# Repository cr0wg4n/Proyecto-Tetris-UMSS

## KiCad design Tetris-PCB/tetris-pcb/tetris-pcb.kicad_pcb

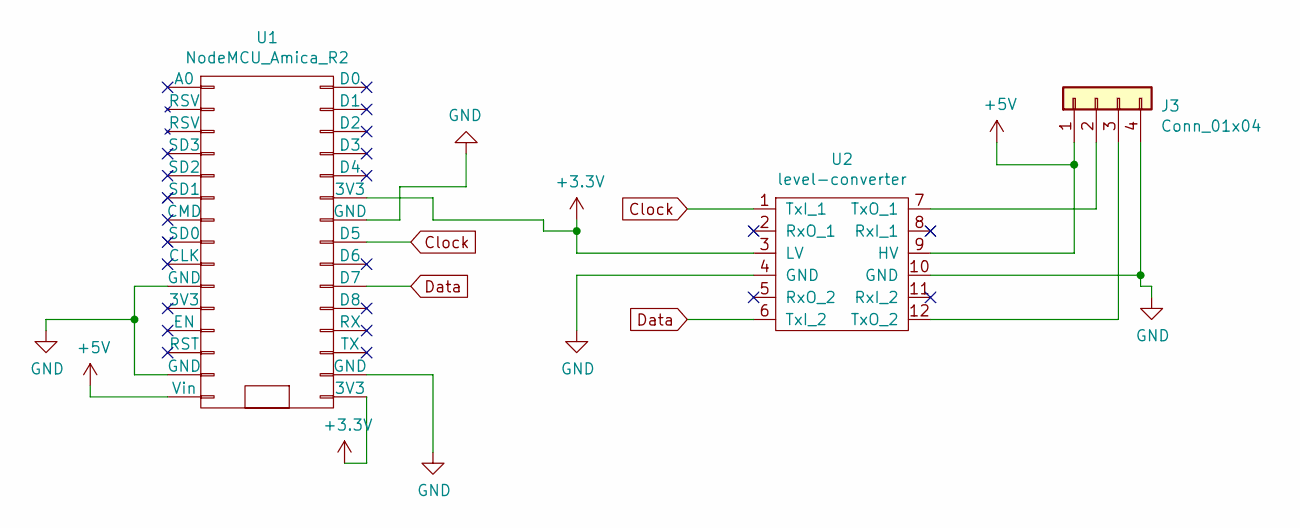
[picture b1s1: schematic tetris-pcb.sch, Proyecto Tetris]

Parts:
J3: Conn_01x04; Molex_KK-254_AE-6410-04A_1x04_P2.54mm_Vertical
U1: NodeMCU_Amica_R2
U2: level-converter; level_converter

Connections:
+3V3: U1.16 (3V3), U1.25 (3V3), U2.3 (LV)
+5V: J3.1, U1.15 (Vin), U2.9 (HV)
Clock: U1.23 (D5), U2.1 (TxI_1)
Data: U1.21 (D7), U2.6 (TxI_2)
GND: J3.4, U1.10 (GND), U1.14 (GND), U1.17 (GND), U1.24 (GND), U2.4 (GND), U2.10 (GND)
unnamed: J3.2, U2.7 (TxO_1)
unnamed: J3.3, U2.12 (TxO_2)

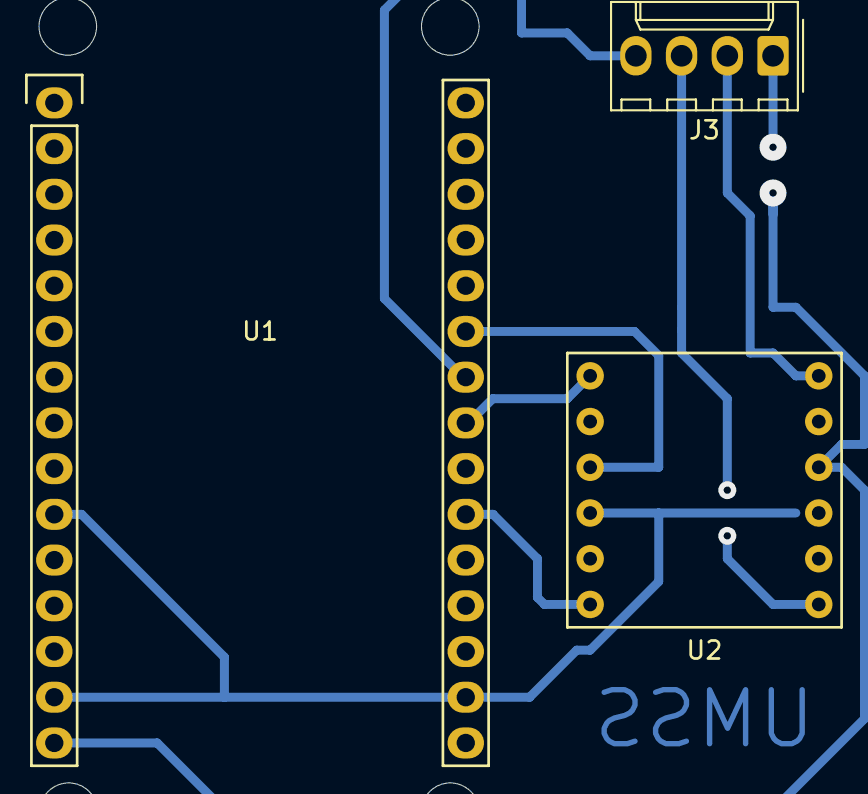
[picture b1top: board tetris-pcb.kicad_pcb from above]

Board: 2 copper layers, 3 parts (0 on the bottom side), 7 nets.

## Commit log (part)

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2019-05-28 server agregado
2019-05-30 agregando codigo para el hardware
2019-06-01 add library
2019-06-01 Tetris Backend
2019-06-02 cambios sabado en grupo
2019-06-02 remove vscode data
2019-06-03 agregando algoritmo de conversion de matriz
2019-06-08 Refactoring Tetris
2019-06-08 agregando python .gitignore y requeriments.txt
2019-06-08 verificando repo
2019-06-20 agregando stm32duino
2019-06-20 moviendo tetris hardware
2019-06-20 SPI interface added to STM
2019-06-22 Add ESP8266 WIFI client
2019-06-23 modicando el servidor para deply
2019-06-23 add gitignore to esp8266
2019-06-23 eliminando archivos inecesarios
2019-06-23 agregando ejemplo de control led
2019-06-23 interfaz de usuario
2019-06-26 add CORS permisions
2019-06-26 servicios agregados
2019-06-27 aumento de keys
2019-06-27 draw matrix
2019-06-28 algoritmo de serializacion pasado a python
2019-06-28 buscando mejoras de performance
2019-06-28 ya envia y dibuja
2019-06-28 WIFI dedicado
2019-06-28 [ADD] Backend Tetris
2019-06-30 agregando tetris
2019-06-30 array format
2019-07-14 Agregado bootstrap y algo de estilo
2019-07-14 Mas estilos
2019-07-14 Aun mas estilo
2019-07-23 cambios con el team
2019-07-26 UI-control-2
2019-07-26 Interfaz para el dibujar la pantalla
2019-07-27 Funcionalidad de selección de color para cada led
2019-07-28 Servicio de envio de matriz de leds
2019-07-31 ordenamiento de carpetas
2019-07-31 3d desings added
2019-08-01 agregando visualizador de musica
2019-11-12 increment colors
2021-03-11 Bump elliptic from 6.5.0 to 6.5.4 in /UI-control-Ionic
    Bumps [elliptic](https://github.com/indutny/elliptic) from 6.5.0 to 6.5.4.
    - [Release notes](https://github.com/indutny/elliptic/releases)
    - [Commits](https://github.com/indutny/elliptic/compare/v6.5.0...v6.5.4)
2021-05-09 Bump handlebars from 4.1.2 to 4.7.7 in /UI-control-Ionic
    Bumps [handlebars](https://github.com/wycats/handlebars.js) from 4.1.2 to 4.7.7.
    - [Release notes](https://github.com/wycats/handlebars.js/releases)
    - [Changelog](https://github.com/handlebars-lang/handlebars.js/blob/master/release-notes.md)
    - [Commits](https://github.com/wycats/handlebars.js/compare/v4.1.2...v4.7.7)
2021-05-10 Bump url-parse from 1.4.7 to 1.5.1 in /UI-control-Ionic
    Bumps [url-parse](https://github.com/unshiftio/url-parse) from 1.4.7 to 1.5.1.
    - [Release notes](https://github.com/unshiftio/url-parse/releases)
    - [Commits](https://github.com/unshiftio/url-parse/compare/1.4.7...1.5.1)
2021-05-11 Bump lodash from 4.17.15 to 4.17.21 in /UI-control-Ionic
    Bumps [lodash](https://github.com/lodash/lodash) from 4.17.15 to 4.17.21.
    - [Release notes](https://github.com/lodash/lodash/releases)
    - [Commits](https://github.com/lodash/lodash/compare/4.17.15...4.17.21)
2021-05-11 Bump hosted-git-info from 2.7.1 to 2.8.9 in /UI-control-Ionic
    Bumps [hosted-git-info](https://github.com/npm/hosted-git-info) from 2.7.1 to 2.8.9.
    - [Release notes](https://github.com/npm/hosted-git-info/releases)
    - [Changelog](https://github.com/npm/hosted-git-info/blob/v2.8.9/CHANGELOG.md)
    - [Commits](https://github.com/npm/hosted-git-info/compare/v2.7.1...v2.8.9)
2021-05-26 Bump browserslist from 4.6.6 to 4.16.6 in /UI-control-Ionic
    Bumps [browserslist](https://github.com/browserslist/browserslist) from 4.6.6 to 4.16.6.
    - [Release notes](https://github.com/browserslist/browserslist/releases)
    - [Changelog](https://github.com/browserslist/browserslist/blob/main/CHANGELOG.md)
    - [Commits](https://github.com/browserslist/browserslist/compare/4.6.6...4.16.6)
2021-05-29 Bump dns-packet from 1.3.1 to 1.3.4 in /UI-control-Ionic
    Bumps [dns-packet](https://github.com/mafintosh/dns-packet) from 1.3.1 to 1.3.4.
    - [Release notes](https://github.com/mafintosh/dns-packet/releases)
    - [Changelog](https://github.com/mafintosh/dns-packet/blob/master/CHANGELOG.md)
    - [Commits](https://github.com/mafintosh/dns-packet/compare/v1.3.1...v1.3.4)
2021-10-06 Bump url-parse from 1.4.7 to 1.5.3 in /UI-control-Ionic
    Bumps [url-parse](https://github.com/unshiftio/url-parse) from 1.4.7 to 1.5.3.
    - [Release notes](https://github.com/unshiftio/url-parse/releases)
    - [Commits](https://github.com/unshiftio/url-parse/compare/1.4.7...1.5.3)
    ---
    updated-dependencies:
    - dependency-name: url-parse
2022-01-14 Bump follow-redirects from 1.7.0 to 1.14.7 in /UI-control-Ionic
    Bumps [follow-redirects](https://github.com/follow-redirects/follow-redirects) from 1.7.0 to 1.14.7.
    - [Release notes](https://github.com/follow-redirects/follow-redirects/releases)
    - [Commits](https://github.com/follow-redirects/follow-redirects/compare/v1.7.0...v1.14.7)
    ---
    updated-dependencies:
    - dependency-name: follow-redirects
2022-01-15 Bump shelljs from 0.8.3 to 0.8.5 in /UI-control-Ionic
    Bumps [shelljs](https://github.com/shelljs/shelljs) from 0.8.3 to 0.8.5.
    - [Release notes](https://github.com/shelljs/shelljs/releases)
    - [Changelog](https://github.com/shelljs/shelljs/blob/master/CHANGELOG.md)
    - [Commits](https://github.com/shelljs/shelljs/compare/v0.8.3...v0.8.5)
    ---
    updated-dependencies:
2022-02-11 Bump karma from 4.1.0 to 6.3.14 in /UI-control-Ionic
    Bumps [karma](https://github.com/karma-runner/karma) from 4.1.0 to 6.3.14.
    - [Release notes](https://github.com/karma-runner/karma/releases)
    - [Changelog](https://github.com/karma-runner/karma/blob/master/CHANGELOG.md)
    - [Commits](https://github.com/karma-runner/karma/compare/v4.1.0...v6.3.14)
    ---
    updated-dependencies:
2022-02-13 Bump follow-redirects from 1.7.0 to 1.14.8 in /UI-control-Ionic
    Bumps [follow-redirects](https://github.com/follow-redirects/follow-redirects) from 1.7.0 to 1.14.8.
    - [Release notes](https://github.com/follow-redirects/follow-redirects/releases)
    - [Commits](https://github.com/follow-redirects/follow-redirects/compare/v1.7.0...v1.14.8)
    ---
    updated-dependencies:
    - dependency-name: follow-redirects
2022-02-27 Bump url-parse from 1.4.7 to 1.5.10 in /UI-control-Ionic
    Bumps [url-parse](https://github.com/unshiftio/url-parse) from 1.4.7 to 1.5.10.
    - [Release notes](https://github.com/unshiftio/url-parse/releases)
    - [Commits](https://github.com/unshiftio/url-parse/compare/1.4.7...1.5.10)
    ---
    updated-dependencies:
    - dependency-name: url-parse
2022-03-02 Bump karma from 4.1.0 to 6.3.16 in /UI-control-Ionic
    Bumps [karma](https://github.com/karma-runner/karma) from 4.1.0 to 6.3.16.
    - [Release notes](https://github.com/karma-runner/karma/releases)
    - [Changelog](https://github.com/karma-runner/karma/blob/master/CHANGELOG.md)
    - [Commits](https://github.com/karma-runner/karma/compare/v4.1.0...v6.3.16)
    ---
    updated-dependencies:
2022-06-01 Bump eventsource from 1.0.7 to 1.1.1 in /UI-control-Ionic
    Bumps [eventsource](https://github.com/EventSource/eventsource) from 1.0.7 to 1.1.1.
    - [Release notes](https://github.com/EventSource/eventsource/releases)
    - [Changelog](https://github.com/EventSource/eventsource/blob/master/HISTORY.md)
    - [Commits](https://github.com/EventSource/eventsource/compare/v1.0.7...v1.1.1)
    ---
    updated-dependencies:
2022-06-03 Bump @angular/core from 7.2.15 to 11.0.5 in /UI-control-Ionic
    Bumps [@angular/core](https://github.com/angular/angular/tree/HEAD/packages/core) from 7.2.15 to 11.0.5.
    - [Release notes](https://github.com/angular/angular/releases)
    - [Changelog](https://github.com/angular/angular/blob/main/CHANGELOG.md)
    - [Commits](https://github.com/angular/angular/commits/11.0.5/packages/core)
    ---
    updated-dependencies:
2022-09-08 Bump jszip from 3.2.2 to 3.10.1 in /UI-control-Ionic
    Bumps [jszip](https://github.com/Stuk/jszip) from 3.2.2 to 3.10.1.
    - [Release notes](https://github.com/Stuk/jszip/releases)
    - [Changelog](https://github.com/Stuk/jszip/blob/main/CHANGES.md)
    - [Commits](https://github.com/Stuk/jszip/compare/v3.2.2...v3.10.1)
    ---
    updated-dependencies:
2022-10-30 Bump socket.io-parser and karma in /UI-control-Ionic
    Bumps [socket.io-parser](https://github.com/socketio/socket.io-parser) to 4.2.1 and updates ancestor dependency [karma](https://github.com/karma-runner/karma). These dependencies need to be updated t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
    Updates `socket.io-parser` from 3.2.0 to 4.2.1
    - [Release notes](https://github.com/socketio/socket.io-parser/releases)
    - [Changelog](https://github.com/socketio/socket.io-parser/blob/main/CHANGELOG.md)
    - [Commits](https://github.com/socketio/socket.io-parser/compare/3.2.0...4.2.1)
    Updates `karma` from 4.1.0 to 6.4.1
2022-11-23 Bump engine.io and karma in /UI-control-Ionic
    Bumps [engine.io](https://github.com/socketio/engine.io) to 6.2.1 and updates ancestor dependency [karma](https://github.com/karma-runner/karma). These dependencies need to be updated together.
    Updates `engine.io` from 3.2.1 to 6.2.1
    - [Release notes](https://github.com/socketio/engine.io/releases)
    - [Changelog](https://github.com/socketio/engine.io/blob/main/CHANGELOG.md)
    - [Commits](https://github.com/socketio/engine.io/compare/3.2.1...6.2.1)
    Updates `karma` from 4.1.0 to 6.4.1
2022-12-06 Bump qs, body-parser and express in /Tetris-Server
    Bumps [qs](https://github.com/ljharb/qs) to 6.11.0 and updates ancestor dependencies [qs](https://github.com/ljharb/qs), [body-parser](https://github.com/expressjs/body-parser) and [express](https://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
    Updates `qs` from 6.7.0 to 6.11.0
    - [Release notes](https://github.com/ljharb/qs/releases)
    - [Changelog](https://github.com/ljharb/qs/blob/main/CHANGELOG.md)
    - [Commits](https://github.com/ljharb/qs/compare/v6.7.0...v6.11.0)
    Updates `body-parser` from 1.19.0 to 1.20.1
2022-12-06 Bump decode-uri-component from 0.2.0 to 0.2.2 in /UI-control-Ionic
    Bumps [decode-uri-component](https://github.com/SamVerschueren/decode-uri-component) from 0.2.0 to 0.2.2.
    - [Release notes](https://github.com/SamVerschueren/decode-uri-component/releases)
    - [Commits](https://github.com/SamVerschueren/decode-uri-component/compare/v0.2.0...v0.2.2)
    ---
    updated-dependencies:
    - dependency-name: decode-uri-component
2022-12-10 Bump express from 4.17.0 to 4.17.3 in /Tetris-Server
    Bumps [express](https://github.com/expressjs/express) from 4.17.0 to 4.17.3.
    - [Release notes](https://github.com/expressjs/express/releases)
    - [Changelog](https://github.com/expressjs/express/blob/master/History.md)
    - [Commits](https://github.com/expressjs/express/compare/4.17.0...4.17.3)
    ---
    updated-dependencies:
2022-12-11 Bump qs from 6.5.2 to 6.5.3 in /UI-control-Ionic
    Bumps [qs](https://github.com/ljharb/qs) from 6.5.2 to 6.5.3.
    - [Release notes](https://github.com/ljharb/qs/releases)
    - [Changelog](https://github.com/ljharb/qs/blob/main/CHANGELOG.md)
    - [Commits](https://github.com/ljharb/qs/compare/v6.5.2...v6.5.3)
    ---
    updated-dependencies:
2023-01-01 Bump json5 and @angular-devkit/build-angular in /UI-control-Ionic
    Bumps [json5](https://github.com/json5/json5) to 2.2.3 and updates ancestor dependency [@angular-devkit/build-angular](https://github.com/angular/angular-cli). These dependencies need to be updated t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
    Updates `json5` from 1.0.1 to 2.2.3
    - [Release notes](https://github.com/json5/json5/releases)
    - [Changelog](https://github.com/json5/json5/blob/main/CHANGELOG.md)
    - [Commits](https://github.com/json5/json5/compare/v1.0.1...v2.2.3)
    Updates `@angular-devkit/build-angular` from 0.13.9 to 15.0.4
